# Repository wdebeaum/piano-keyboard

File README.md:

# Modular Piano Keyboard

By William de Beaumont

[CC BY 4.0](https://creativecommons.org/licenses/by/4.0/)

## Description

A DIY portable electronic piano keyboard with full-size keys, composed of several identical single-octave modules plugged together. Made using 3D printing, through-hole soldering, and easily obtainable parts.

Each key has two switches that close at different heights, in order to detect the velocity with which the key is pressed. Each octave (12 keys) has 3 8-bit shift registers that take input from the 24 switches in parallel, and shift output out serially, down towards the low (left) side of the keyboard.

That side may be connected to an end piece that uses a Teensy 4.0 to drive the shift registers and act as a USB MIDI controller. The end piece also has pitch bend and modulation wheels, a connection for a sustain pedal, and buttons to adjust a few settings.

Alternatively, you can connect that side of the keyboard to your own microcontroller, using an SPI port and one GPIO pin. The included `spi2midi` program will turn keypresses into MIDI commands on `stdout` if it is run on a Raspberry Pi connected to the keyboard as shown in [`wiring.h`](wiring.h).

## Instructions

 - [Bill of Materials](BOM.md)

 - [Building Instructions](BUILD.md) (many pictures)

 - [Usage Instructions](USAGE.md)

## Known issues

 - The key switches sometimes get out of alignment, preventing specific keys from triggering consistently until you take the key off and realign the switch.

 - The connection between the lowest octave and the end piece is a bit wobbly with only one alignment pin.

 - The pitch bend knob has no centering mechanism. I tried to make various kinds of springs for it, but the results were unsatisfying.

 - The hole in the end piece enclosure intended to let the LED on the Teensy shine through is too far away from it to matter. Maybe a light pipe would improve it. But as it is, the light shines out the right side anyway, so whatever.

## Future work

 - Better integration with ALSA MIDI ports on RasPi, ultimately letting it act as a standalone musical instrument by connecting to a soft synth.

 - Surface-mount version of octave PCB for mass production? Switches are still labor-intensive, though.

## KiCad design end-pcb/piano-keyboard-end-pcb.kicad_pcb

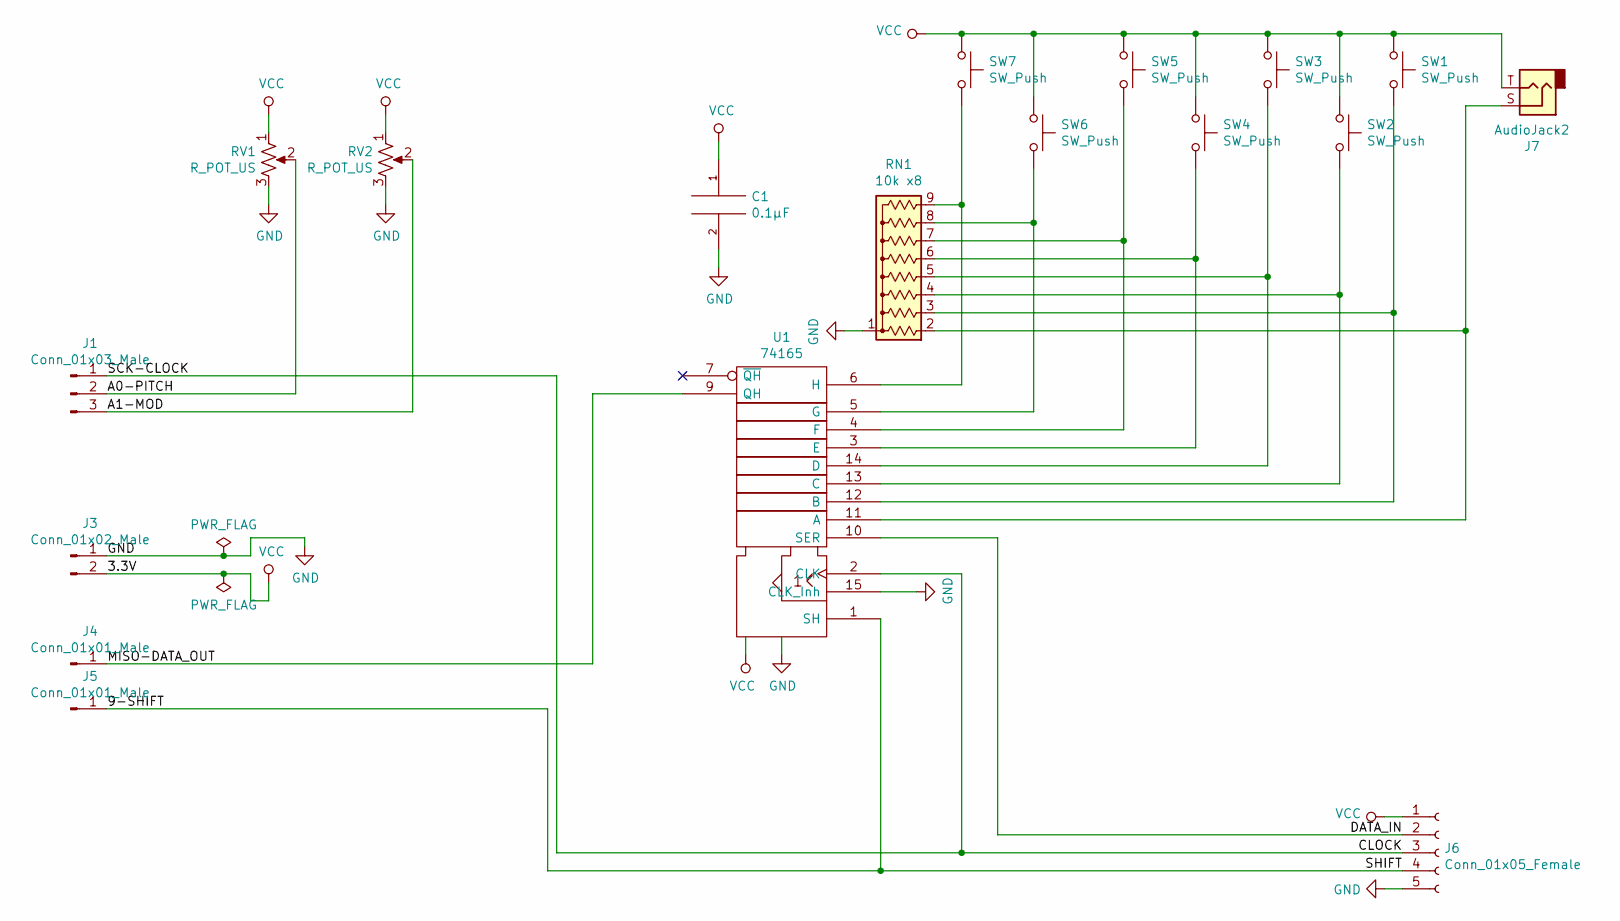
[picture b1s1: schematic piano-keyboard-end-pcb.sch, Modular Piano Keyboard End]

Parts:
C1: 0.1μF; C_Disc_D3.8mm_W2.6mm_P2.50mm
J1: Conn_01x03_Male; PinHeader_1x03_P2.54mm_Vertical
J3: Conn_01x02_Male; PinHeader_1x02_P2.54mm_Vertical
J4, J5: Conn_01x01_Male; PinHeader_1x01_P2.54mm_Vertical
J6: Conn_01x05_Female; PinSocket_1x05_P2.54mm_Horizontal
J7: AudioJack2; Switchcraft_RA49B11
RN1: 10k x8; R_Array_SIP9
RV1, RV2: R_POT_US; Potentiometer_Bourns_PTV09A-2_Single_Horizontal
SW1, SW2, SW3, SW4, SW5, SW6, SW7: SW_Push; SW_PUSH_6mm
U1: 74165; DIP-16_W7.62mm

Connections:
/9-SHIFT: J5.1, J6.4, U1.1 (SH)
/A0-PITCH: J1.2, RV1.2
/A1-MOD: J1.3, RV2.2
/CLOCK: J1.1, J6.3, U1.2 (CLK)
/DATA_IN: J6.2, U1.10 (SER)
/MISO-DATA_OUT: J4.1, U1.9 (QH)
GND: C1.2, J3.1, J6.5, RN1.1 (common), RV1.3, RV2.3, U1.8 (GND), U1.15 (CLK_Inh)
unnamed: J7.S, RN1.2 (R1), U1.11 (A)
unnamed: RN1.3 (R2), SW1.2, U1.12 (B)
unnamed: RN1.4 (R3), SW2.2, U1.13 (C)
unnamed: RN1.5 (R4), SW3.2, U1.14 (D)
unnamed: RN1.6 (R5), SW4.2, U1.3 (E)
unnamed: RN1.7 (R6), SW5.2, U1.4 (F)
unnamed: RN1.8 (R7), SW6.2, U1.5 (G)
unnamed: RN1.9 (R8), SW7.2, U1.6 (H)
VCC: C1.1, J3.2, J6.1, J7.T, RV1.1, RV2.1, SW1.1, SW2.1, SW3.1, SW4.1, SW5.1, SW6.1, SW7.1, U1.16 (VCC)

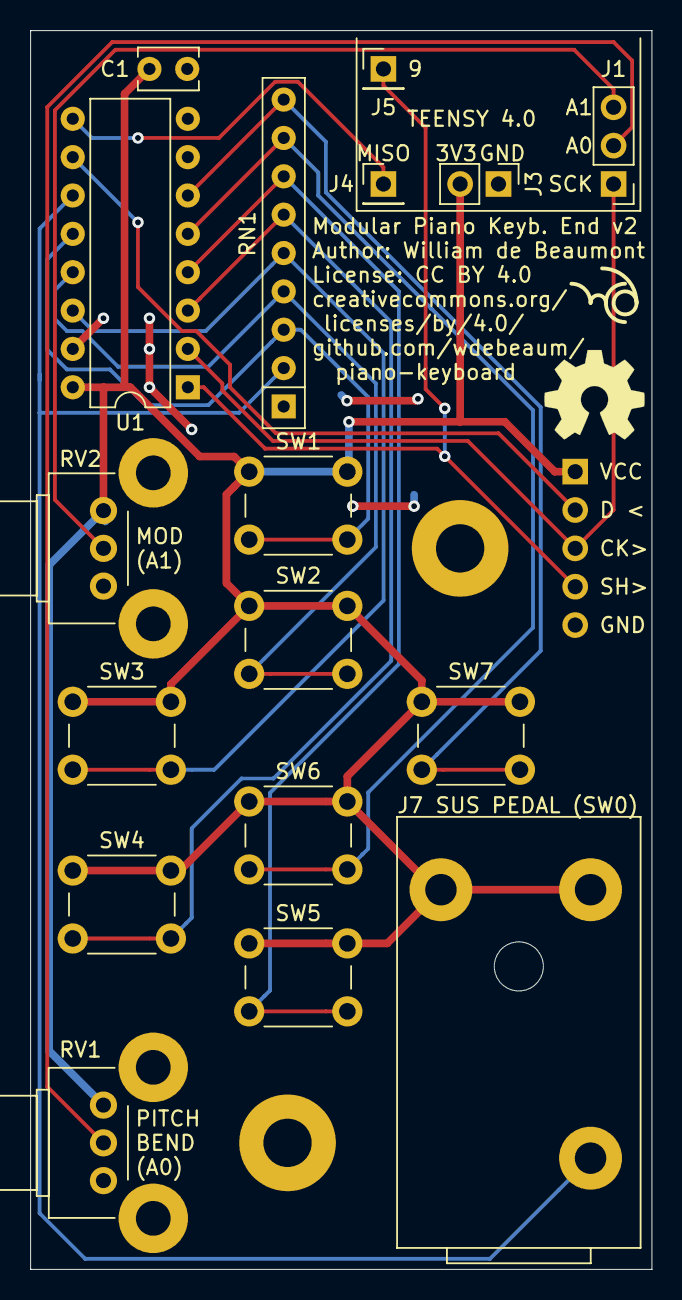
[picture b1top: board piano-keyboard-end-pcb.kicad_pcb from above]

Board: 2 copper layers, 41.1 x 82.0 mm, 18 parts (1 on the bottom side), 16 nets.

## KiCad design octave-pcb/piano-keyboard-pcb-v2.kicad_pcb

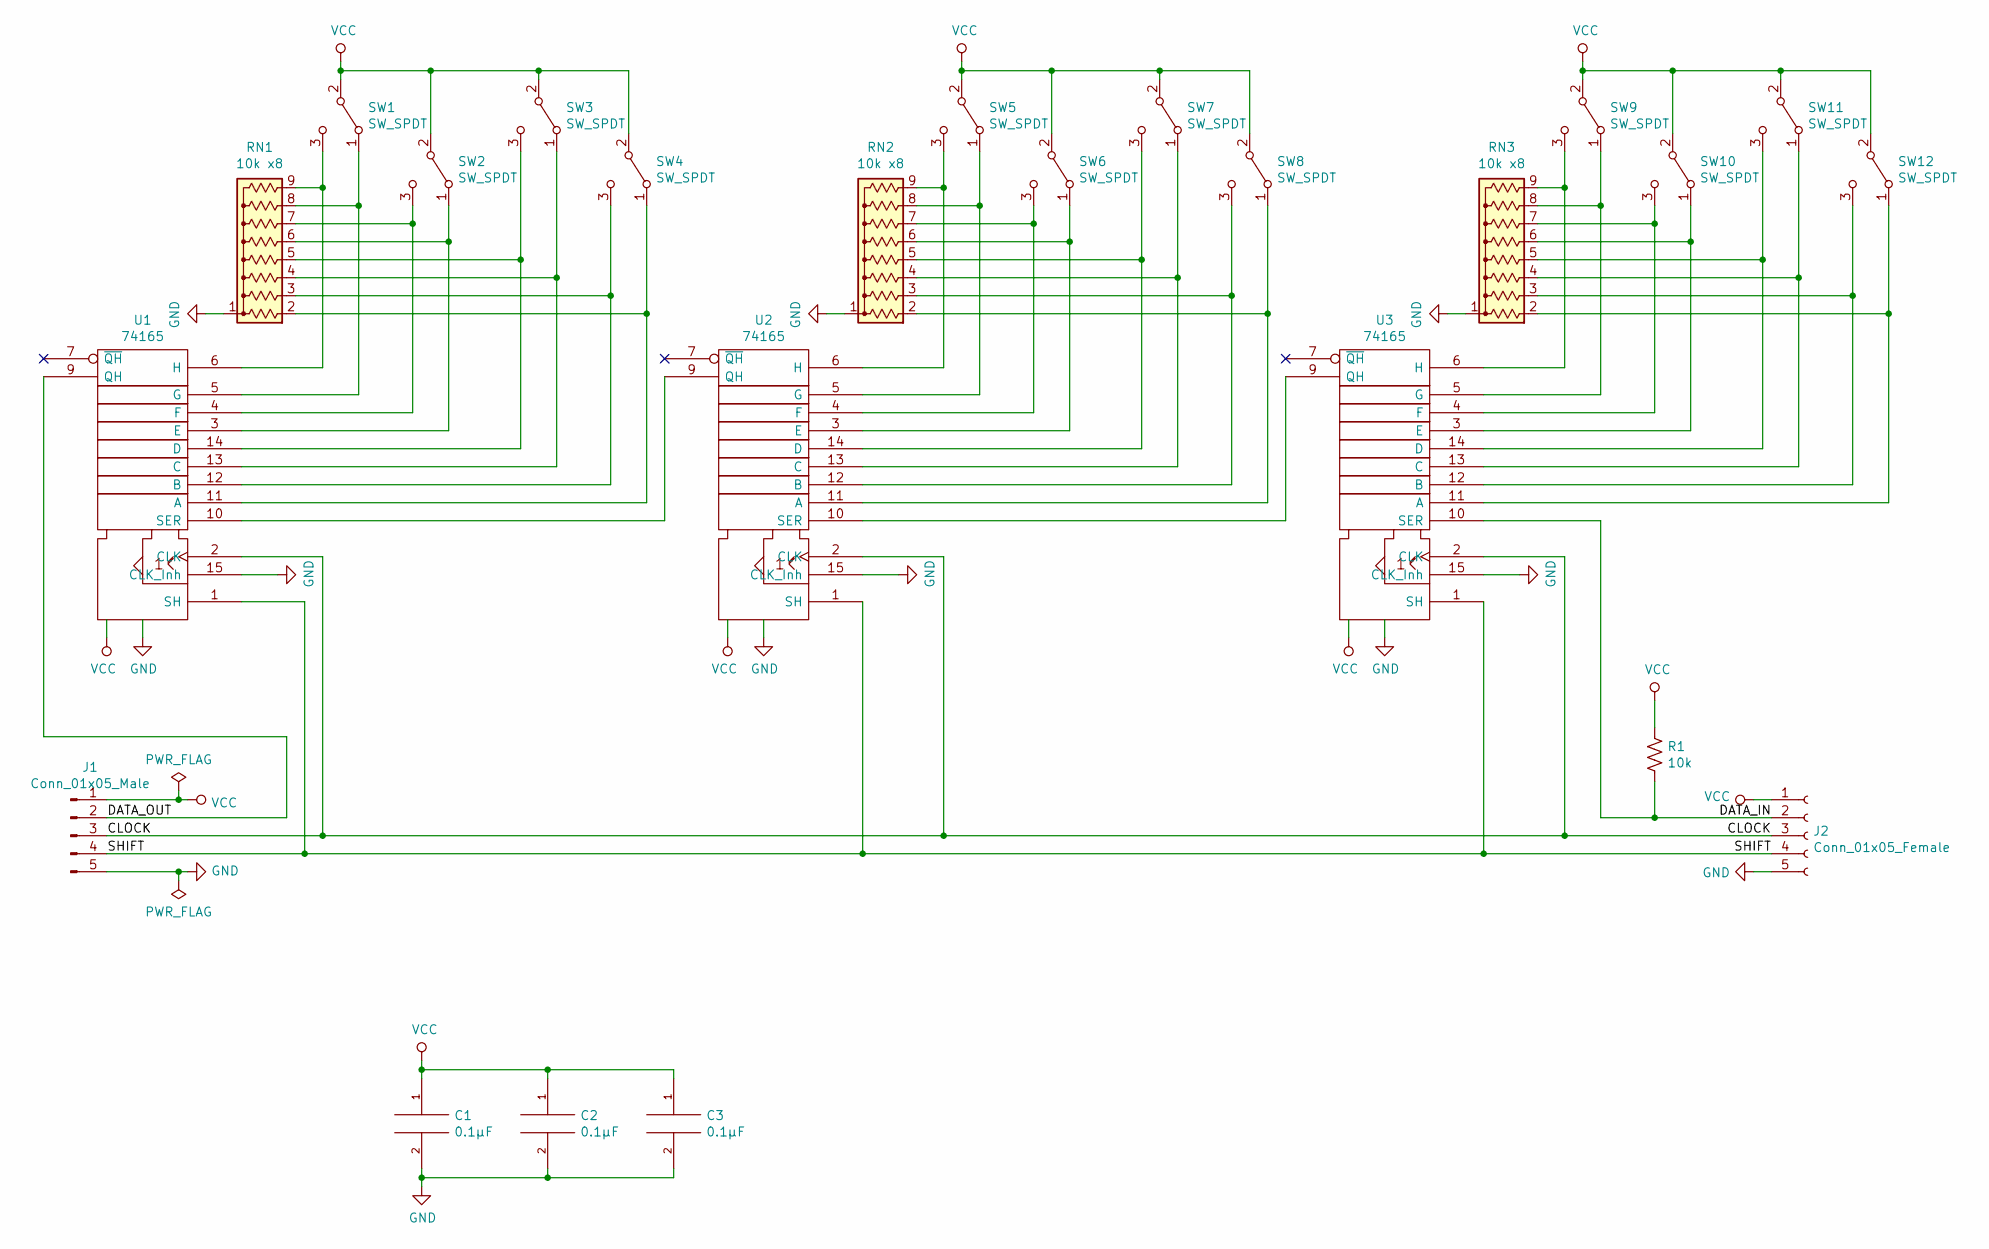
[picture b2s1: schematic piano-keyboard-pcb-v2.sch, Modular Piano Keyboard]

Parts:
C1, C2, C3: 0.1μF; C_Disc_D3.8mm_W2.6mm_P2.50mm
J1: Conn_01x05_Male; PinHeader_1x05_P2.54mm_Horizontal
J2: Conn_01x05_Female; PinSocket_1x05_P2.54mm_Horizontal
R1: 10k; R_Axial_DIN0207_L6.3mm_D2.5mm_P7.62mm_Horizontal
RN1, RN2, RN3: 10k x8; R_Array_SIP9
SW1, SW2, SW3, SW4, SW5, SW6, SW7, SW8, SW9, SW10, SW11, SW12: SW_SPDT; keysw213
U1, U2, U3: 74165; DIP-16_W7.62mm

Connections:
/CLOCK: J1.3, J2.3, U1.2 (CLK), U2.2 (CLK), U3.2 (CLK)
/DATA_IN: J2.2, R1.2, U3.10 (SER)
/DATA_OUT: J1.2, U1.9 (QH)
/SHIFT: J1.4, J2.4, U1.1 (SH), U2.1 (SH), U3.1 (SH)
GND: C1.2, C2.2, C3.2, J1.5, J2.5, RN1.1 (common), RN2.1 (common), RN3.1 (common), U1.8 (GND), U1.15 (CLK_Inh), U2.8 (GND), U2.15 (CLK_Inh), U3.8 (GND), U3.15 (CLK_Inh)
unnamed: RN1.2 (R1), SW4.1 (A), U1.11 (A)
unnamed: RN1.3 (R2), SW4.3 (C), U1.12 (B)
unnamed: RN1.4 (R3), SW3.1 (A), U1.13 (C)
unnamed: RN1.5 (R4), SW3.3 (C), U1.14 (D)
unnamed: RN1.6 (R5), SW2.1 (A), U1.3 (E)
unnamed: RN1.7 (R6), SW2.3 (C), U1.4 (F)
unnamed: RN1.8 (R7), SW1.1 (A), U1.5 (G)
unnamed: RN1.9 (R8), SW1.3 (C), U1.6 (H)
unnamed: RN2.2 (R1), SW8.1 (A), U2.11 (A)
unnamed: RN2.3 (R2), SW8.3 (C), U2.12 (B)
unnamed: RN2.4 (R3), SW7.1 (A), U2.13 (C)
unnamed: RN2.5 (R4), SW7.3 (C), U2.14 (D)
unnamed: RN2.6 (R5), SW6.1 (A), U2.3 (E)
unnamed: RN2.7 (R6), SW6.3 (C), U2.4 (F)
unnamed: RN2.8 (R7), SW5.1 (A), U2.5 (G)
unnamed: RN2.9 (R8), SW5.3 (C), U2.6 (H)
unnamed: RN3.2 (R1), SW12.1 (A), U3.11 (A)
unnamed: RN3.3 (R2), SW12.3 (C), U3.12 (B)
unnamed: RN3.4 (R3), SW11.1 (A), U3.13 (C)
unnamed: RN3.5 (R4), SW11.3 (C), U3.14 (D)
unnamed: RN3.6 (R5), SW10.1 (A), U3.3 (E)
unnamed: RN3.7 (R6), SW10.3 (C), U3.4 (F)
unnamed: RN3.8 (R7), SW9.1 (A), U3.5 (G)
unnamed: RN3.9 (R8), SW9.3 (C), U3.6 (H)
unnamed: U1.10 (SER), U2.9 (QH)
unnamed: U2.10 (SER), U3.9 (QH)
VCC: C1.1, C2.1, C3.1, J1.1, J2.1, R1.1, SW1.2 (B), SW2.2 (B), SW3.2 (B), SW4.2 (B), SW5.2 (B), SW6.2 (B), SW7.2 (B), SW8.2 (B), SW9.2 (B), SW10.2 (B), SW11.2 (B), SW12.2 (B), U1.16 (VCC), U2.16 (VCC), U3.16 (VCC)

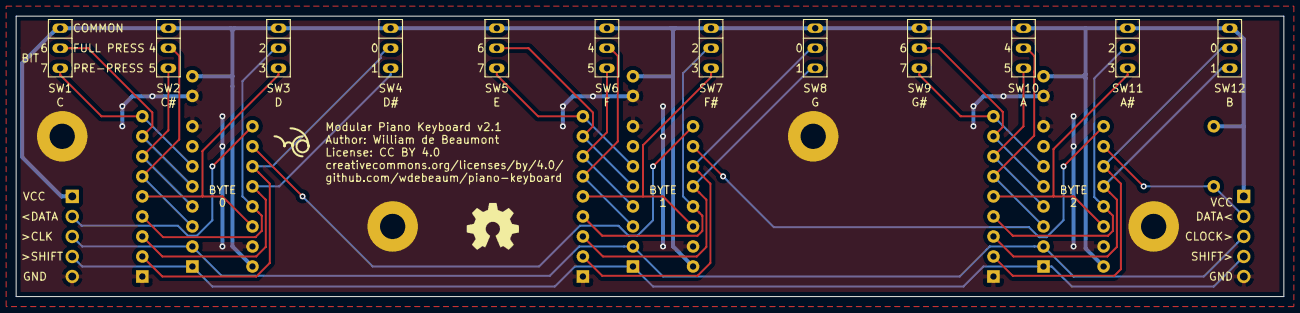
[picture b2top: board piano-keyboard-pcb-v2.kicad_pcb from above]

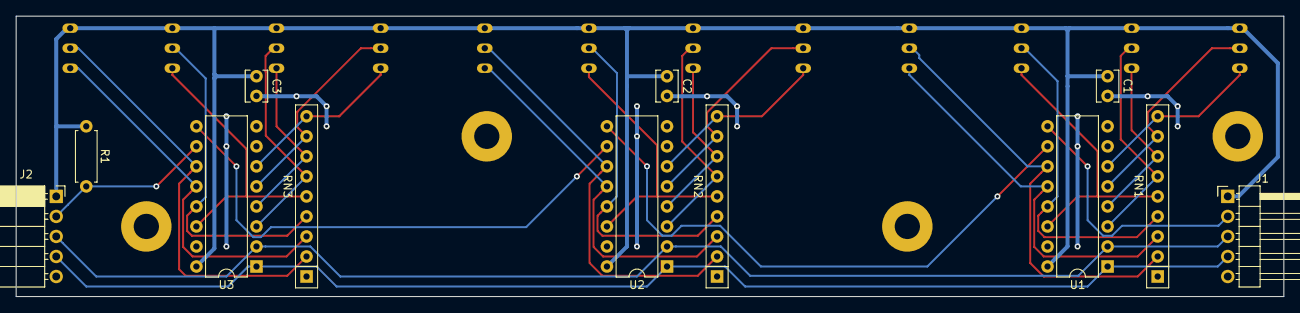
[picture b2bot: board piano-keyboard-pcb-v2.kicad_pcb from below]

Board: 2 copper layers, 160.8 x 35.6 mm, 24 parts (12 on the bottom side), 32 nets.

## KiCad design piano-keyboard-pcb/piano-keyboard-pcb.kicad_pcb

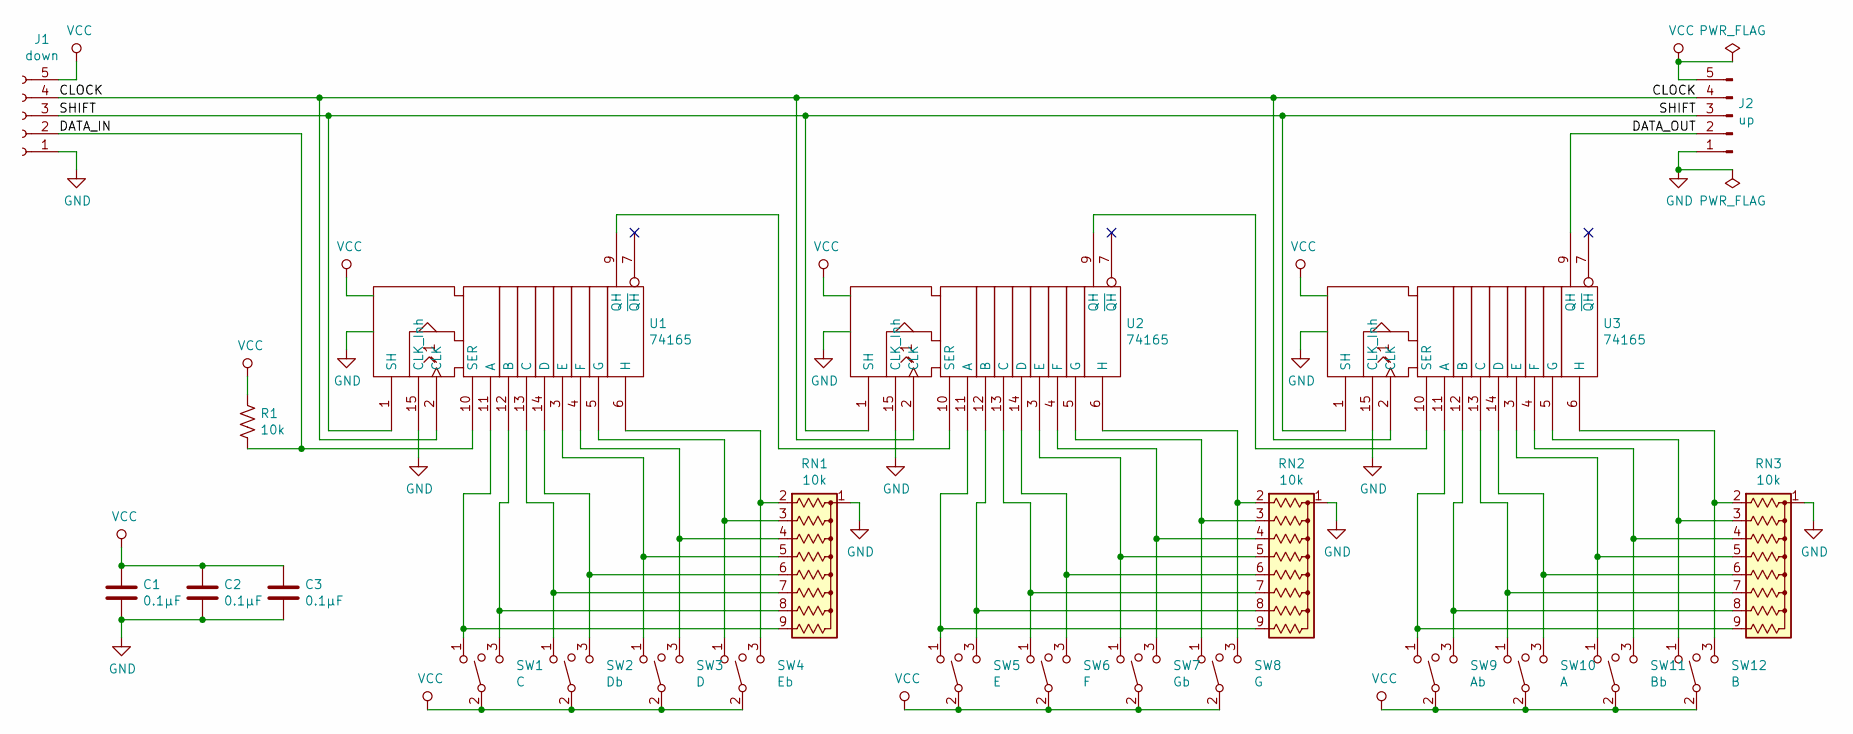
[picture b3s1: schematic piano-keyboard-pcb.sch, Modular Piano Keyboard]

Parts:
C1, C2, C3: 0.1μF; C_Disc_D3.8mm_W2.6mm_P2.50mm
J1: down; PinSocket_1x05_P2.54mm_Horizontal
J2: up; PinHeader_1x05_P2.54mm_Horizontal
R1: 10k; R_Axial_DIN0204_L3.6mm_D1.6mm_P5.08mm_Horizontal
RN1, RN2, RN3: 10k; SIP9_Housing
SW1: C; PinHeader_1x03_P2.54mm_Vertical
SW2: Db; PinHeader_1x03_P2.54mm_Vertical
SW3: D; PinHeader_1x03_P2.54mm_Vertical
SW4: Eb; PinHeader_1x03_P2.54mm_Vertical
SW5: E; PinHeader_1x03_P2.54mm_Vertical
SW6: F; PinHeader_1x03_P2.54mm_Vertical
SW7: Gb; PinHeader_1x03_P2.54mm_Vertical
SW8: G; PinHeader_1x03_P2.54mm_Vertical
SW9: Ab; PinHeader_1x03_P2.54mm_Vertical
SW10: A; PinHeader_1x03_P2.54mm_Vertical
SW11: Bb; PinHeader_1x03_P2.54mm_Vertical
SW12: B; PinHeader_1x03_P2.54mm_Vertical
U1, U2, U3: 74165; DIP-16_W7.62mm

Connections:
/CLOCK: J1.4, J2.4, U1.2 (CLK), U2.2 (CLK), U3.2 (CLK)
/DATA_IN: J1.2, R1.2, U1.10 (SER)
/DATA_OUT: J2.2, U3.9 (QH)
/SHIFT: J1.3, J2.3, U1.1 (SH), U2.1 (SH), U3.1 (SH)
GND: C1.2, C2.2, C3.2, J1.1, J2.1, RN1.1 (common), RN2.1 (common), RN3.1 (common), U1.8 (GND), U1.15 (CLK_Inh), U2.8 (GND), U2.15 (CLK_Inh), U3.8 (GND), U3.15 (CLK_Inh)
unnamed: RN1.2 (R1), SW4.3, U1.6 (H)
unnamed: RN1.3 (R2), SW4.1, U1.5 (G)
unnamed: RN1.4 (R3), SW3.3, U1.4 (F)
unnamed: RN1.5 (R4), SW3.1, U1.3 (E)
unnamed: RN1.6 (R5), SW2.3, U1.14 (D)
unnamed: RN1.7 (R6), SW2.1, U1.13 (C)
unnamed: RN1.8 (R7), SW1.3, U1.12 (B)
unnamed: RN1.9 (R8), SW1.1, U1.11 (A)
unnamed: RN2.2 (R1), SW8.3, U2.6 (H)
unnamed: RN2.3 (R2), SW8.1, U2.5 (G)
unnamed: RN2.4 (R3), SW7.3, U2.4 (F)
unnamed: RN2.5 (R4), SW7.1, U2.3 (E)
unnamed: RN2.6 (R5), SW6.3, U2.14 (D)
unnamed: RN2.7 (R6), SW6.1, U2.13 (C)
unnamed: RN2.8 (R7), SW5.3, U2.12 (B)
unnamed: RN2.9 (R8), SW5.1, U2.11 (A)
unnamed: RN3.2 (R1), SW12.3, U3.6 (H)
unnamed: RN3.3 (R2), SW12.1, U3.5 (G)
unnamed: RN3.4 (R3), SW11.3, U3.4 (F)
unnamed: RN3.5 (R4), SW11.1, U3.3 (E)
unnamed: RN3.6 (R5), SW10.3, U3.14 (D)
unnamed: RN3.7 (R6), SW10.1, U3.13 (C)
unnamed: RN3.8 (R7), SW9.3, U3.12 (B)
unnamed: RN3.9 (R8), SW9.1, U3.11 (A)
unnamed: U1.9 (QH), U2.10 (SER)
unnamed: U2.9 (QH), U3.10 (SER)
VCC: C1.1, C2.1, C3.1, J1.5, J2.5, R1.1, SW1.2, SW2.2, SW3.2, SW4.2, SW5.2, SW6.2, SW7.2, SW8.2, SW9.2, SW10.2, SW11.2, SW12.2, U1.16 (VCC), U2.16 (VCC), U3.16 (VCC)

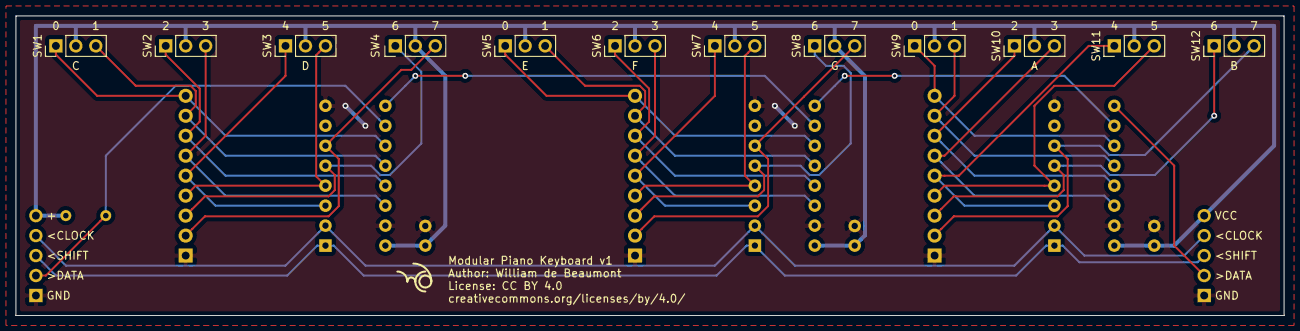
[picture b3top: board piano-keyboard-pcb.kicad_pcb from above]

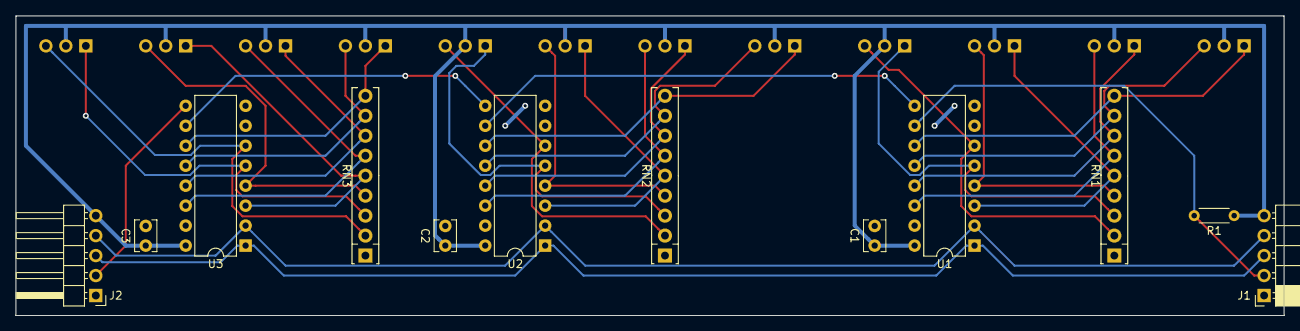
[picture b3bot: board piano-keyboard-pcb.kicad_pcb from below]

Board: 2 copper layers, 161.3 x 38.1 mm, 24 parts (12 on the bottom side), 32 nets.

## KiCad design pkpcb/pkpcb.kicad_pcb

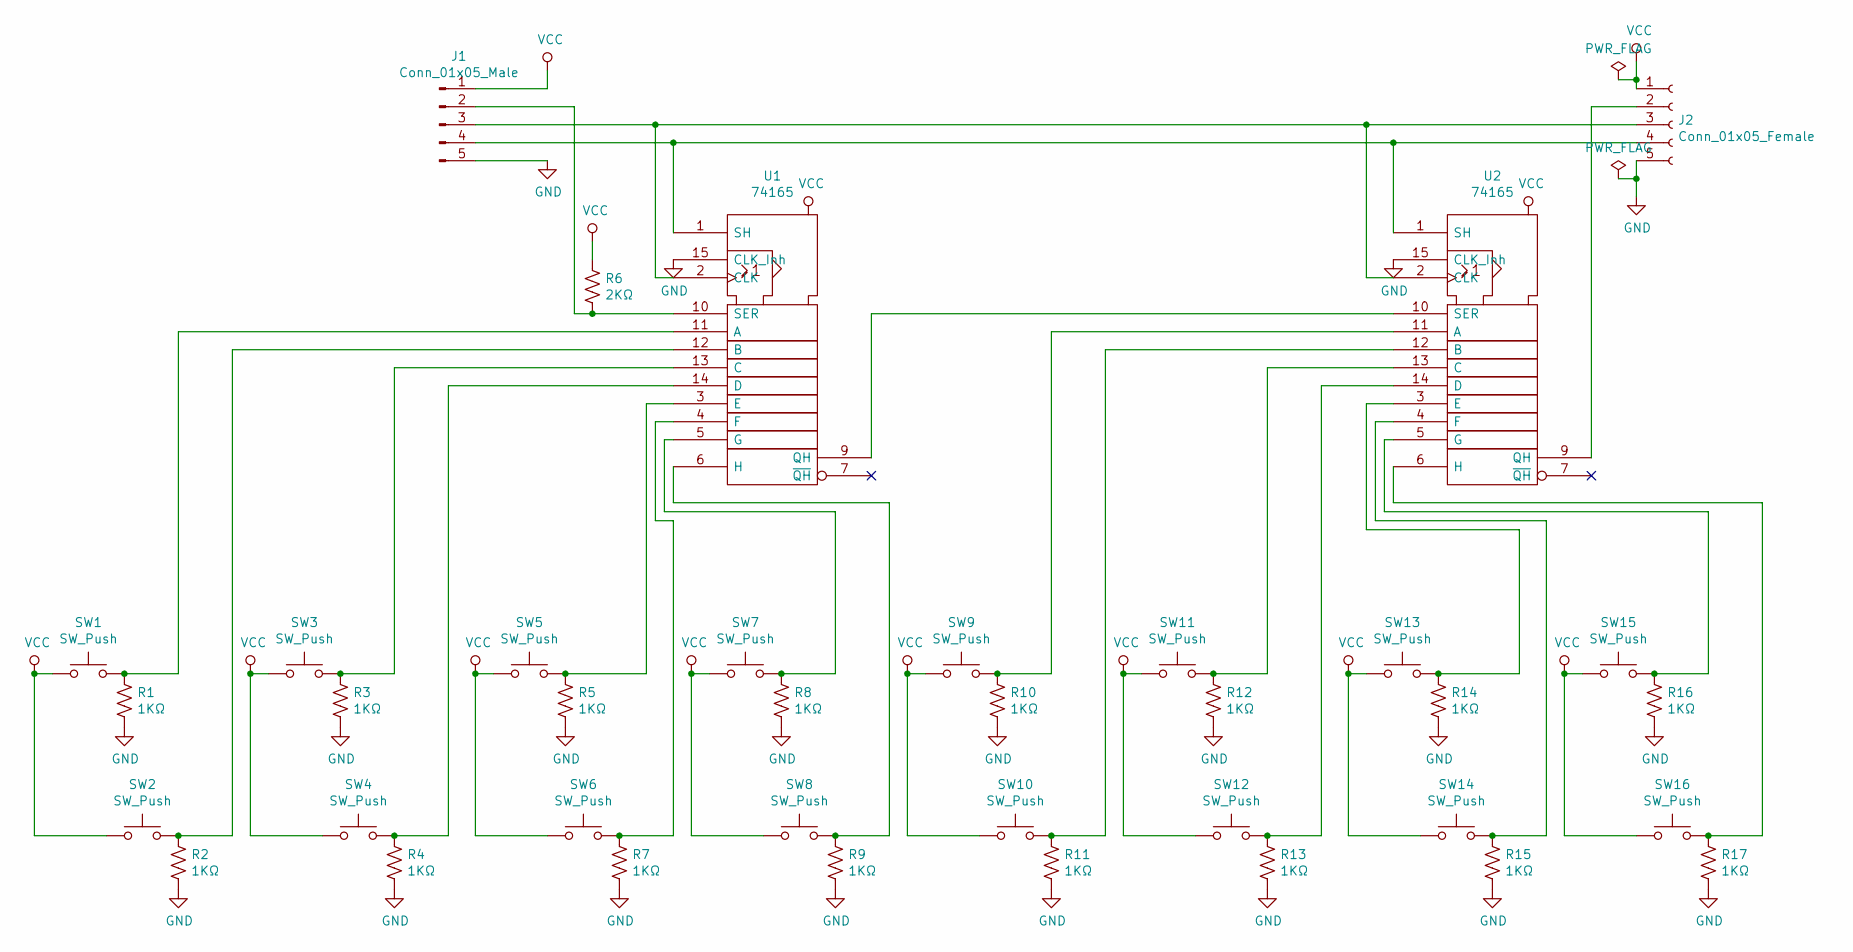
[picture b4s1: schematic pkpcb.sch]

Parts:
J1: Conn_01x05_Male; PinHeader_1x05_P2.54mm_Horizontal
J2: Conn_01x05_Female; PinSocket_1x05_P2.54mm_Horizontal
R1, R2, R3, R4, R5, R7, R8, R9, R10, R11, R12, R13, R14, R15, R16, R17: 1KΩ; R_0603_1608Metric
R6: 2KΩ; R_0603_1608Metric
SW1, SW2, SW3, SW4, SW5, SW6, SW7, SW8, SW9, SW10, SW11, SW12, SW13, SW14, SW15, SW16: SW_Push; TestPoint_2Pads_Pitch5.08mm_Drill1.3mm
U1, U2: 74165; SOIC-16_3.9x9.9mm_P1.27mm

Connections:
GND: J1.5, J2.5, R1.2, R2.2, R3.2, R4.2, R5.2, R7.2, R8.2, R9.2, R10.2, R11.2, R12.2, R13.2, R14.2, R15.2, R16.2, R17.2, U1.8 (GND), U1.15 (CLK_Inh), U2.8 (GND), U2.15 (CLK_Inh)
unnamed: J1.2, R6.2, U1.10 (SER)
unnamed: J1.3, J2.3, U1.2 (CLK), U2.2 (CLK)
unnamed: J1.4, J2.4, U1.1 (SH), U2.1 (SH)
unnamed: J2.2, U2.9 (QH)
unnamed: R1.1, SW1.2, U1.11 (A)
unnamed: R2.1, SW2.2, U1.12 (B)
unnamed: R3.1, SW3.2, U1.13 (C)
unnamed: R4.1, SW4.2, U1.14 (D)
unnamed: R5.1, SW5.2, U1.3 (E)
unnamed: R7.1, SW6.2, U1.4 (F)
unnamed: R8.1, SW7.2, U1.5 (G)
unnamed: R9.1, SW8.2, U1.6 (H)
unnamed: R10.1, SW9.2, U2.11 (A)
unnamed: R11.1, SW10.2, U2.12 (B)
unnamed: R12.1, SW11.2, U2.13 (C)
unnamed: R13.1, SW12.2, U2.14 (D)
unnamed: R14.1, SW13.2, U2.3 (E)
unnamed: R15.1, SW14.2, U2.4 (F)
unnamed: R16.1, SW15.2, U2.5 (G)
unnamed: R17.1, SW16.2, U2.6 (H)
unnamed: U1.9 (QH), U2.10 (SER)
VCC: J1.1, J2.1, R6.1, SW1.1, SW2.1, SW3.1, SW4.1, SW5.1, SW6.1, SW7.1, SW8.1, SW9.1, SW10.1, SW11.1, SW12.1, SW13.1, SW14.1, SW15.1, SW16.1, U1.16 (VCC), U2.16 (VCC)

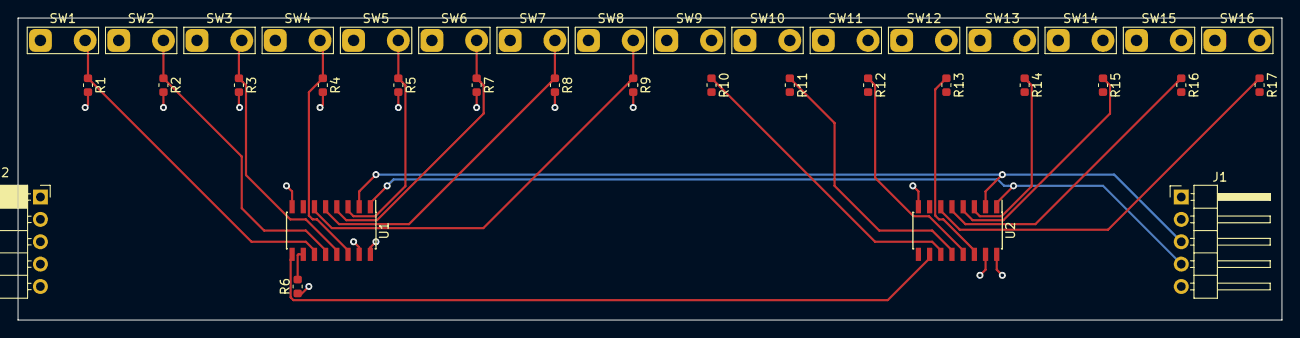
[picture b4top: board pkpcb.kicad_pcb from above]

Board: 4 copper layers, 143.5 x 34.3 mm, 37 parts (0 on the bottom side), 23 nets.

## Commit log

2020-03-06 20170129/piano-keyboard.scad
2020-03-06 20170129/piano-keyboard.cleaned.scad
2020-03-06 20170204/piano-keyboard.scad
2020-03-06 20170204/piano-keyboard.with-notes.scad
2020-03-06 20170209/piano-keyboard.scad
2020-03-06 20170211/cardboard-base-measurements.rb
2020-03-06 20170211/piano-keyboard.scad
2020-03-06 20170212/piano-keyboard.scad
2020-03-06 20170218/piano-keyboard.scad
2020-03-06 20170218-2/piano-keyboard.scad
2020-03-06 20170219/piano-keyboard.scad
2020-03-06 20200215/piano-keyboard.scad.borked
2020-03-06 20200215/piano-keyboard.scad
2020-03-06 20200216/piano-keyboard.scad
2020-03-06 20200216-2/piano-keyboard.scad
2020-03-06 20200219/pkpcb/
2020-03-06 piano-keyboard-pcb-v1/
2020-03-06 initial version of program to read keyboard via SPI on RasPi and write MIDI events
2020-03-06 actually call setup_gpio() (d'oh!); fix endianness
2020-03-06 scan slower so velocity is more reasonable
2020-03-06 try to debounce by only emitting an event in the second scan in a new state
2020-03-06 write midi events to stdout
2020-03-06 git unification
    This version is where I am while merging the different parts of this project into one unified git repo. The PCB is at v2, the version first sent to be manufactured. The 3D model is at a point where i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
2020-03-21 update TODO after both printing base and getting pcb made and seeing how they fit
2020-03-21 do what I set out to in prev. commit
2020-03-22 update TODO after printing another base segment
2020-03-26 increase bpin radius more and adjust angle to match; make more notes
2020-03-26 swap sense of key bit pairs in spi2midi.c to match new pcb layout
2020-03-29 better document how sense of key bits is determined; add debug print
2020-03-29 ughghgh, == binds tighter than &
2020-03-30 decide on gluing cardboard to base for stability; print c-f half again
2020-04-03 clean up TODO; print C key
2020-04-05 try printing two keys, not diagonal, to mitigate curl in both directions
2020-04-07 fix MIDI note number calculation
2020-04-19 print high half of base
2020-04-21 print F and G keys
2020-04-25 print last two white keys, A and B
2020-05-03 print 3 black keys
2020-05-07 sample keys faster for better velocity control; use a middle octave
2020-05-07 improve PCB support:
    - switch from pegs to holes for M3 screws
    - cut out a bit of A# key to accommodate screw head
    - make trenches under PCB supports smaller so support is stiffer
    also: explain parameters better in comments
2020-05-08 refactor and document more, and add more ghost parts in assembled version; replace "fit tests" with series of recommended prints
2020-05-17 decrease screw hole radius so that threads bite more
2020-05-17 bridge over peak of teardrop-shaped skewer holes to avoid curling up into bobby pin slots
2020-05-21 echo cardboard dimensions
2020-05-21 add option to print black keys in two prints per octave to avoid curling
2020-05-21 add README.md, and a rule for making README.html from it
2020-05-21 add a tiny inline gif of octaves being plugged together
2020-05-26 start adding better images to README
2020-05-26 add many more images to README, and some other minor edits
2020-05-26 split docs into multiple files
2020-06-06 schematic for PCB at the end, to connect to Teensy 4.0
2020-06-07 start laying out end pcb
2020-06-07 finish adding footprints, including custom one for 1/4" mono jack; do rough part layout
2020-06-07 put most parts on front side, align to 50mil grid
2020-06-07 add traces and silkscreen labels; rearrange buttons to make traces easier
2020-06-07 make a simple 3d model for the 1/4" mono jack
2020-06-07 make a simple 3d model for the pots (KiCAD doesn't actually have this)
2020-06-07 move mod pot right so it aligns with edge and pitch bend pot
2020-06-07 move pitch bend pot up slightly to align with 10mil grid
2020-06-07 rough sketch of end enclosure to make sure I have all the features in the right places
2020-06-08 correct button dimensions
2020-06-09 fix potentiometer shaft radius, and add its length to scad params
2020-06-09 add knobs
2020-06-09 make a big TODO comment about how to finish the end enclosure
2020-06-09 rename piano-keyboard=>octave and piano-keyboard-end=>end
2020-06-09 factor out common.scad from octave.scad and end.scad
2020-06-09 add anchor point on knob for pitch bend centering torsion spring
2020-06-10 make assemblable by extending sus/usb port holes and removing bottom wall; add pcb shelves; taper top around teensy
2020-06-10 much work on enclosure:
    - add skewer
    - make button extension pieces
    - separate button panel from rest of enclosure
    - add separate assembled and plated_* modules
2020-06-10 shape button holes to match button shaft shapes
2020-06-10 add torsion spring anchor hole in enclosure
2020-06-10 remove done TODO comment
2020-06-11 add my logo to the top of the end enclosure
2020-06-11 add cardboard to bottom of assembled end
2020-06-11 rename things named the same in octave and end; add full assembly in assembled.scad; fix an alignment issue that revealed
2020-06-11 start writing code for teensy (collect all the library calls I'll need)
2020-06-12 fill in teensy code, mostly copying from spi2midi
2020-06-14 clear SH/~LD one clock cycle earlier (seems to work better)
2020-06-14 save old pot value (oops); report pot values less frequently, and average over many scans
2020-06-14 set analog input pins' mode to INPUT_DISABLE
    This disables the digital input circuitry on those pins, which was
    causing discontinuities in the analog values around where the digital
    value would switch.
2020-06-14 return -1 from update_pot() when scan_count!=0
    (WTF, how did the compiler not catch the missing return statement?)
2020-06-14 do pot calc with longs; add center midi value when pot value is above center (oops)
2020-06-14 turns out I don't actually need MIDIcontroller.h; usbMIDI is part of standard library
2020-06-14 report pot values a little more frequently
2020-06-15 try using pin 9 instead of MOSI for SH/~LD in order to have better control over its timing; decrease clock from 30MHz to 26MHz, experimentally the highest I can go with this pin arrangement and 3 oct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
2020-06-15 avoid weird usbMIDI.sendPitchBend() behavior by sending the raw MIDI message myself; make sure I send the 1-based channel number to the usbMIDI library (instead of 0-based)
2020-06-15 make end PCB use Teensy pin 9 instead of MOSI, to match the software
    Also move the Teensy down to make room for the new connection, and
    reroute traces and rearrange silkscreen to compensate. Also add the
    github URL where this repo will be to the silkscreen.
2020-06-15 adjust Teensy position to match end PCB; also adjust logo position
2020-06-15 bevel edges of knobs
2020-06-15 use support_gap instead of gap between end and octave, so that connectors don't overlap too much
2020-06-15 don't comment out reading buttons (oops)
2020-06-15 replace 1ms delays with ~22ns busy-waits
2020-06-16 fixes for issues discovered in first print of enclosure:
    - increase width of shelf for button panel (and add left side) so it doesn't fall through
    - increase base radius of screw posts (make them cones) to make them not tip during printing (or ever)
    - increase button panel radius and add cutout in shelf to accommodate bigger front screw post
    - add bottom wall (floor?) on left side to stiffen enclosure and not let button panel push it apart and slip through (but avoid covering screws with this wall)
    - make torsion spring anchor holes bigger to accommodate insulation on wire (AWG rating doesn't include insulation)
    Also add exploded_end() module to better show how to assemble.
2020-06-16 animate exploded_end()
2020-06-16 fix z offset of plated buttons
2020-06-17 fixes after printing knobs and buttons:
    - make buttons heads thicker and wider so they actually print the right shape
    - make retention nubs at ends of button shafts bigger so they actually print
    - increase gaps so things actually fit
2020-06-18 decrease gap between knob ir and pot shaft slightly; print knobs and button panel to test
2020-06-18 more tweaks:
    - make gap between knob and pot shaft slightly smaller still (knob still slipped off too easily)
    - make button shafts slightly longer (concerned they might not hit the buttons)
    - divide triangle button shaft retention nub radius by sqrt(2) so it's not too big (didn't fit in hole)
    - add ghosts showing actual button heights since the model kicad used is too short
    - don't use small_v_hole_shrinkage in z dimension when making button holes
    - make button shaft guides shorter so that ends of button shafts stick out the bottom, and the guides won't accidentally push the buttons
2020-06-27 fixes after printing controls again, and receiving end pcb:
    - increase width of button shafts, narrowing gap
    - increase length of button shafts, so they can reach buttons consistently
    - increase gap on ±Y sides of pcb (including teensy) to account for vertical printing of those slots
2020-06-28 add build instructions for the end piece
2020-06-28 add instructions for installing firmware on teensy for end piece
2020-06-28 add usage instructions for end piece
2020-06-28 fix end cardboard height
2020-06-28 add BOM for end piece
2020-06-28 update README to mention new end piece
2020-06-28 increase thickness of rectangle button shaft too (oops)
2020-06-28 add github link to octave pcb silkscreen; adjust placement of "J2" silkscreen so it doesn't get cut off
2020-06-29 tweak end assembly instructions to better reflect how I actually ended up doing it
2020-06-29 reorder end assembly steps so knobs come after screws, so the enclosure can lay flat on its top while you drive the screws
2020-07-01 set old_button_states (oops)
    Also factor out a bunch of settings related to the SPI/SN74HC165
    interface, and comment on how I've been tweaking them, what the
    datasheet says, and what actually works.
2020-07-01 improve initial behavior of pots:
    - disable pots until we see raw values far to either side of center, to
    exclude noise before pots are calibrated
    - don't use initial value as center if it's way to one side or the
    other; instead use theoretical center
2020-07-02 fix control button behavior:
    - fix maximum values (0x7f, not 0x3f, d'oh!)
    - mod by step size instead of subtracting maximum+1, so e.g.
    transposition preserves octave when wrapping
    - register values are unsigned, so avoid testing if they're <0
2020-07-03 more build instructions tweaks:
    - include measurements for non-printed mechanical parts of end
    - suggest wrapping tape around pot shafts
    - fix old references to "assembled();"
2020-07-03 re-send last note with new settings when control buttons pressed
2020-07-03 rename images/all_parts.jpg to images/octave_parts.jpg
2020-07-04 add picture of end parts to BOM; fix labels in picture of octave parts
2020-07-04 add photos of building end piece
2020-07-04 fix swapped gender of octave connectors in BOM
2020-07-04 talk about resending last note on button presses in USAGE.md
2020-07-04 update recommended clock frequency in USAGE
2020-07-04 fix range of modulation wheel values
2020-07-04 add known issues section to README.md
2020-07-04 update gif in README
2020-07-04 add knob calibration instructions to USAGE.md
2020-07-18 use 3.3V throughout, instead of mixing it with 5V levels
    This fixes the issues with the highest few keys intermittently not
    working. It also makes the end PCB a little simpler. The shift registers
    won't run as fast, but it turns out they don't need to.

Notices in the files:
end-pcb/piano-keyboard-end-pcb.kicad_pcb:
License: CC BY 4.0
creativecommons.org
